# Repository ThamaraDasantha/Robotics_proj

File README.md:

# Robotics_proj

Roboarm algoritham - 
    Esp32 wifi conncet to mobile
Mortor Controller algoritham - 
    
Edeg ditection algoritham -

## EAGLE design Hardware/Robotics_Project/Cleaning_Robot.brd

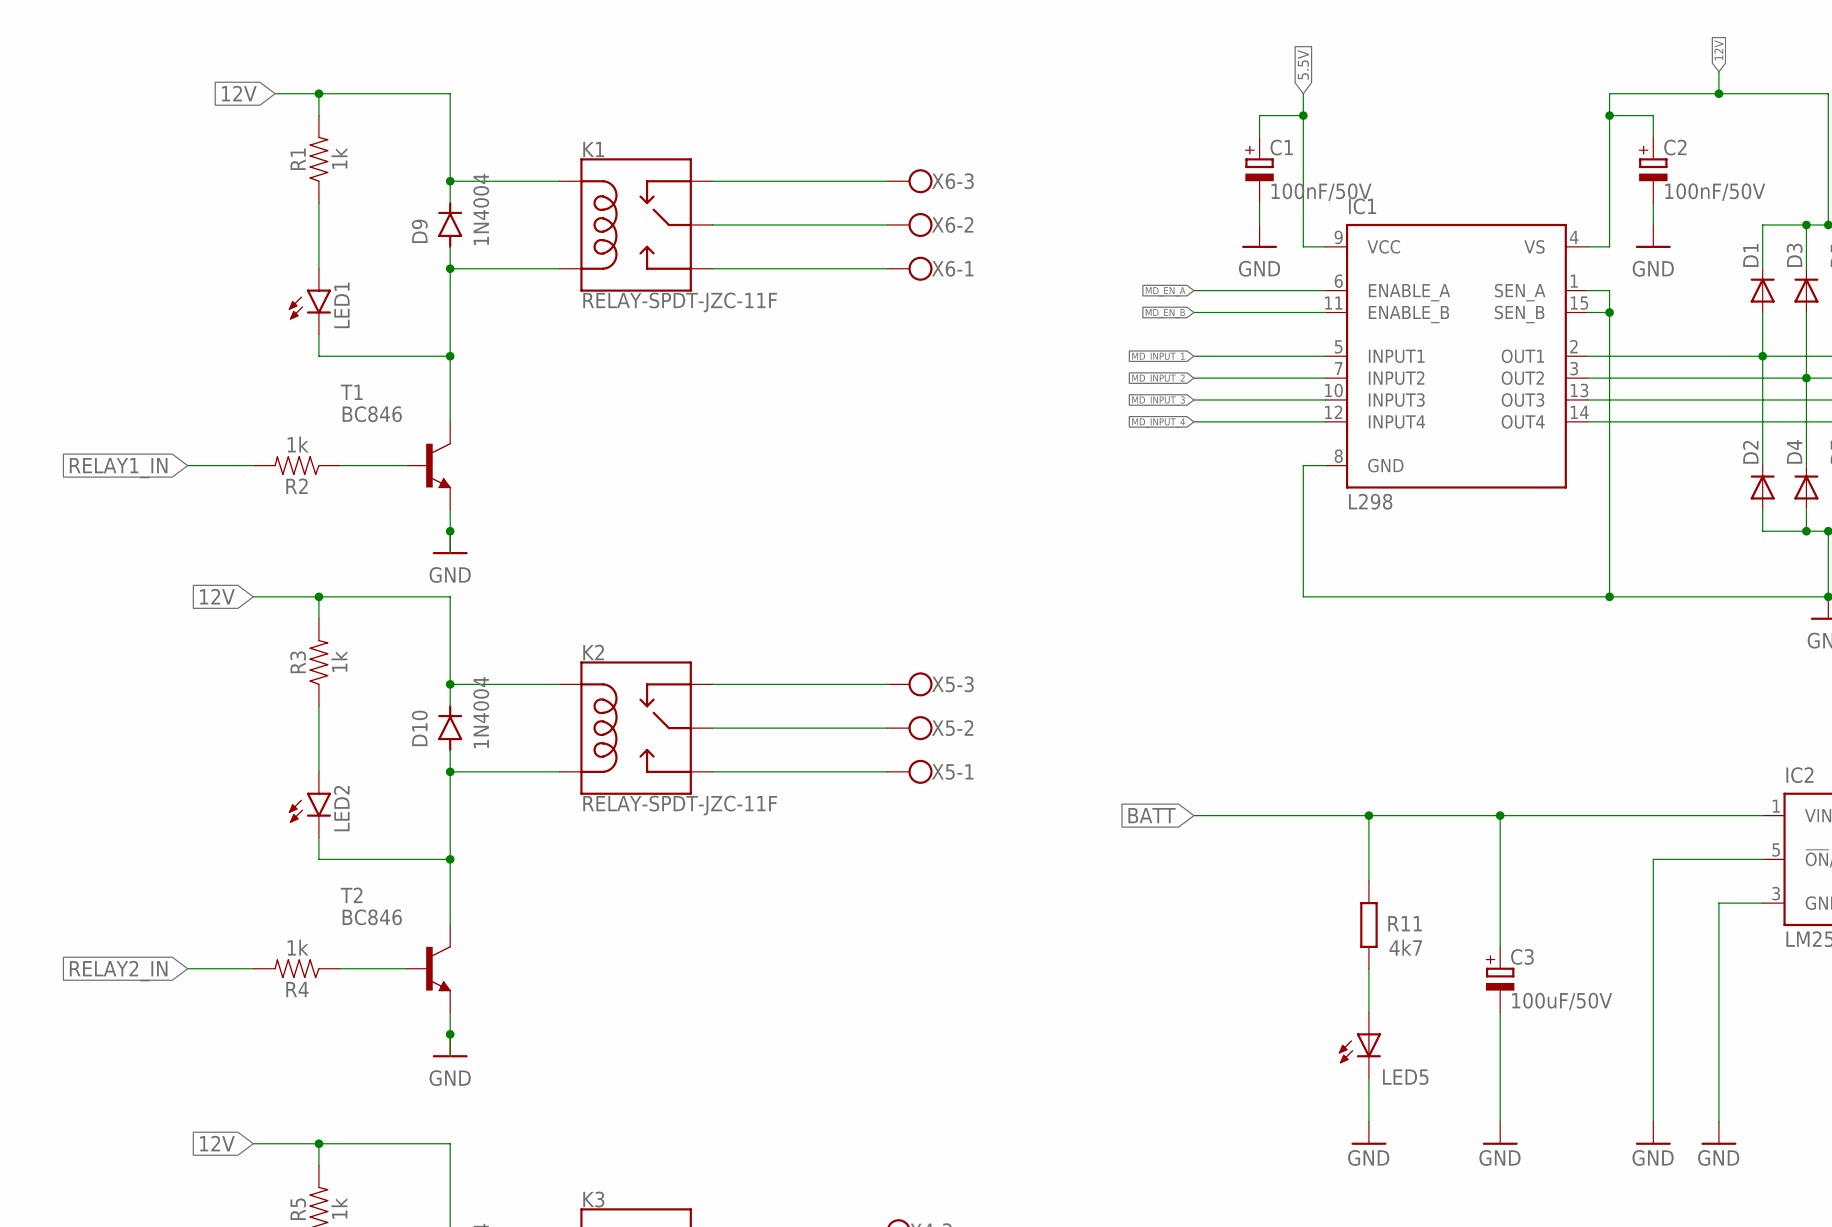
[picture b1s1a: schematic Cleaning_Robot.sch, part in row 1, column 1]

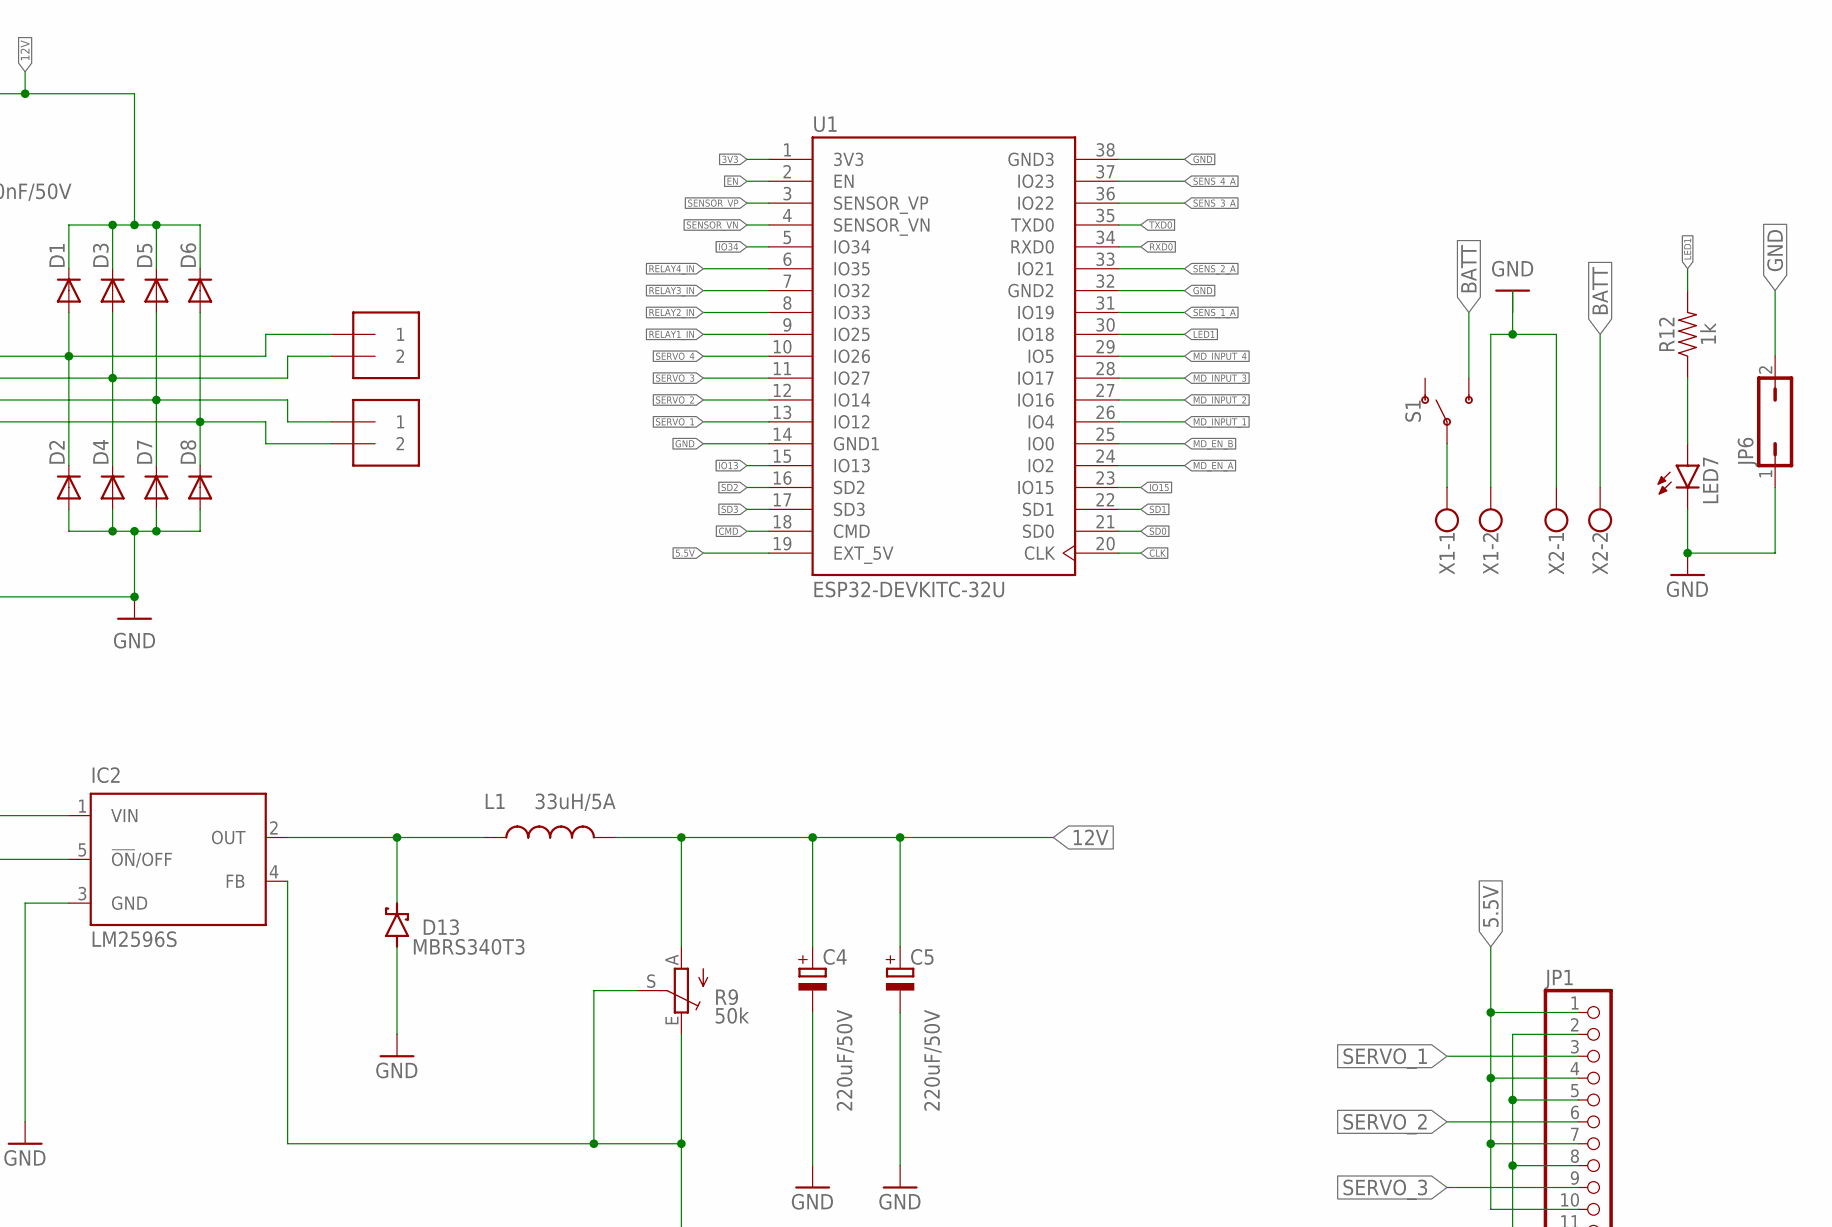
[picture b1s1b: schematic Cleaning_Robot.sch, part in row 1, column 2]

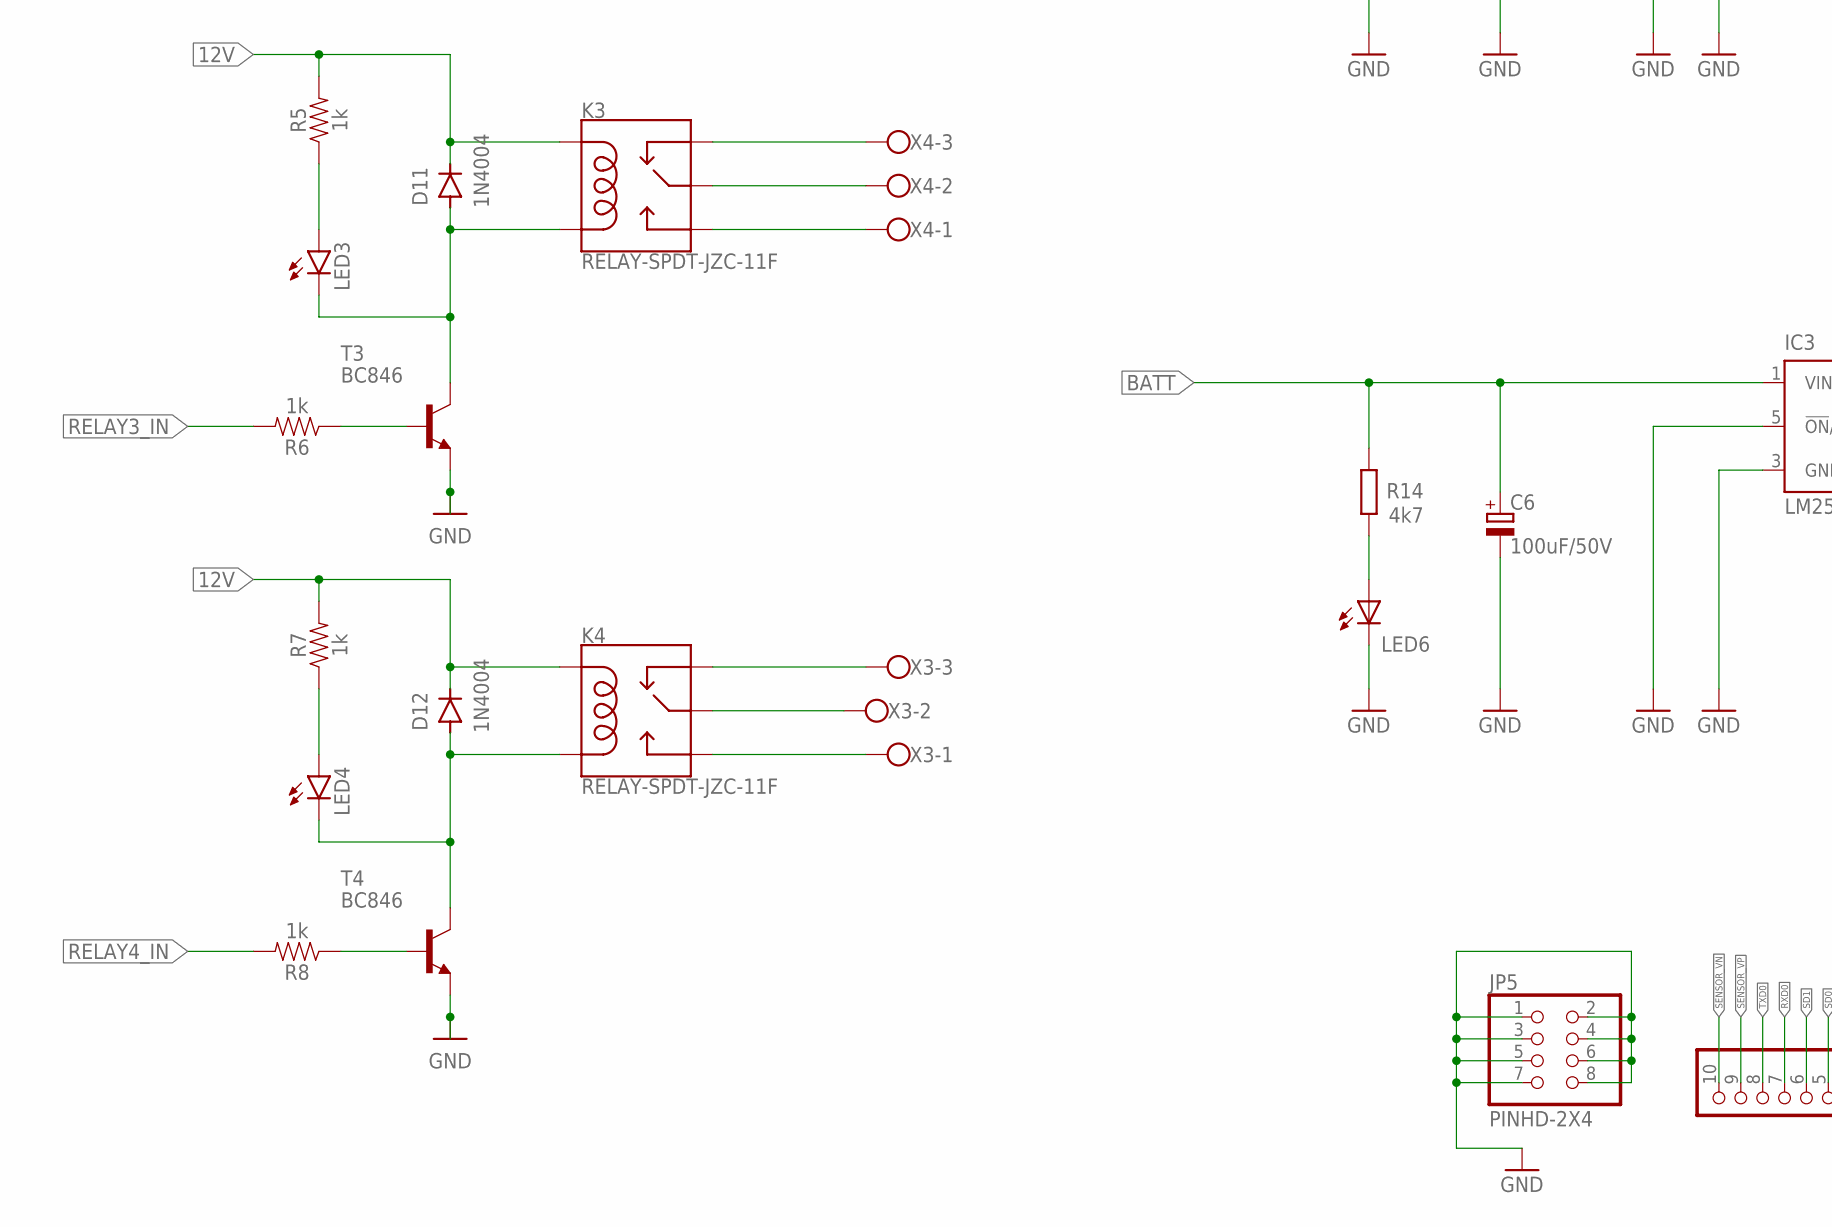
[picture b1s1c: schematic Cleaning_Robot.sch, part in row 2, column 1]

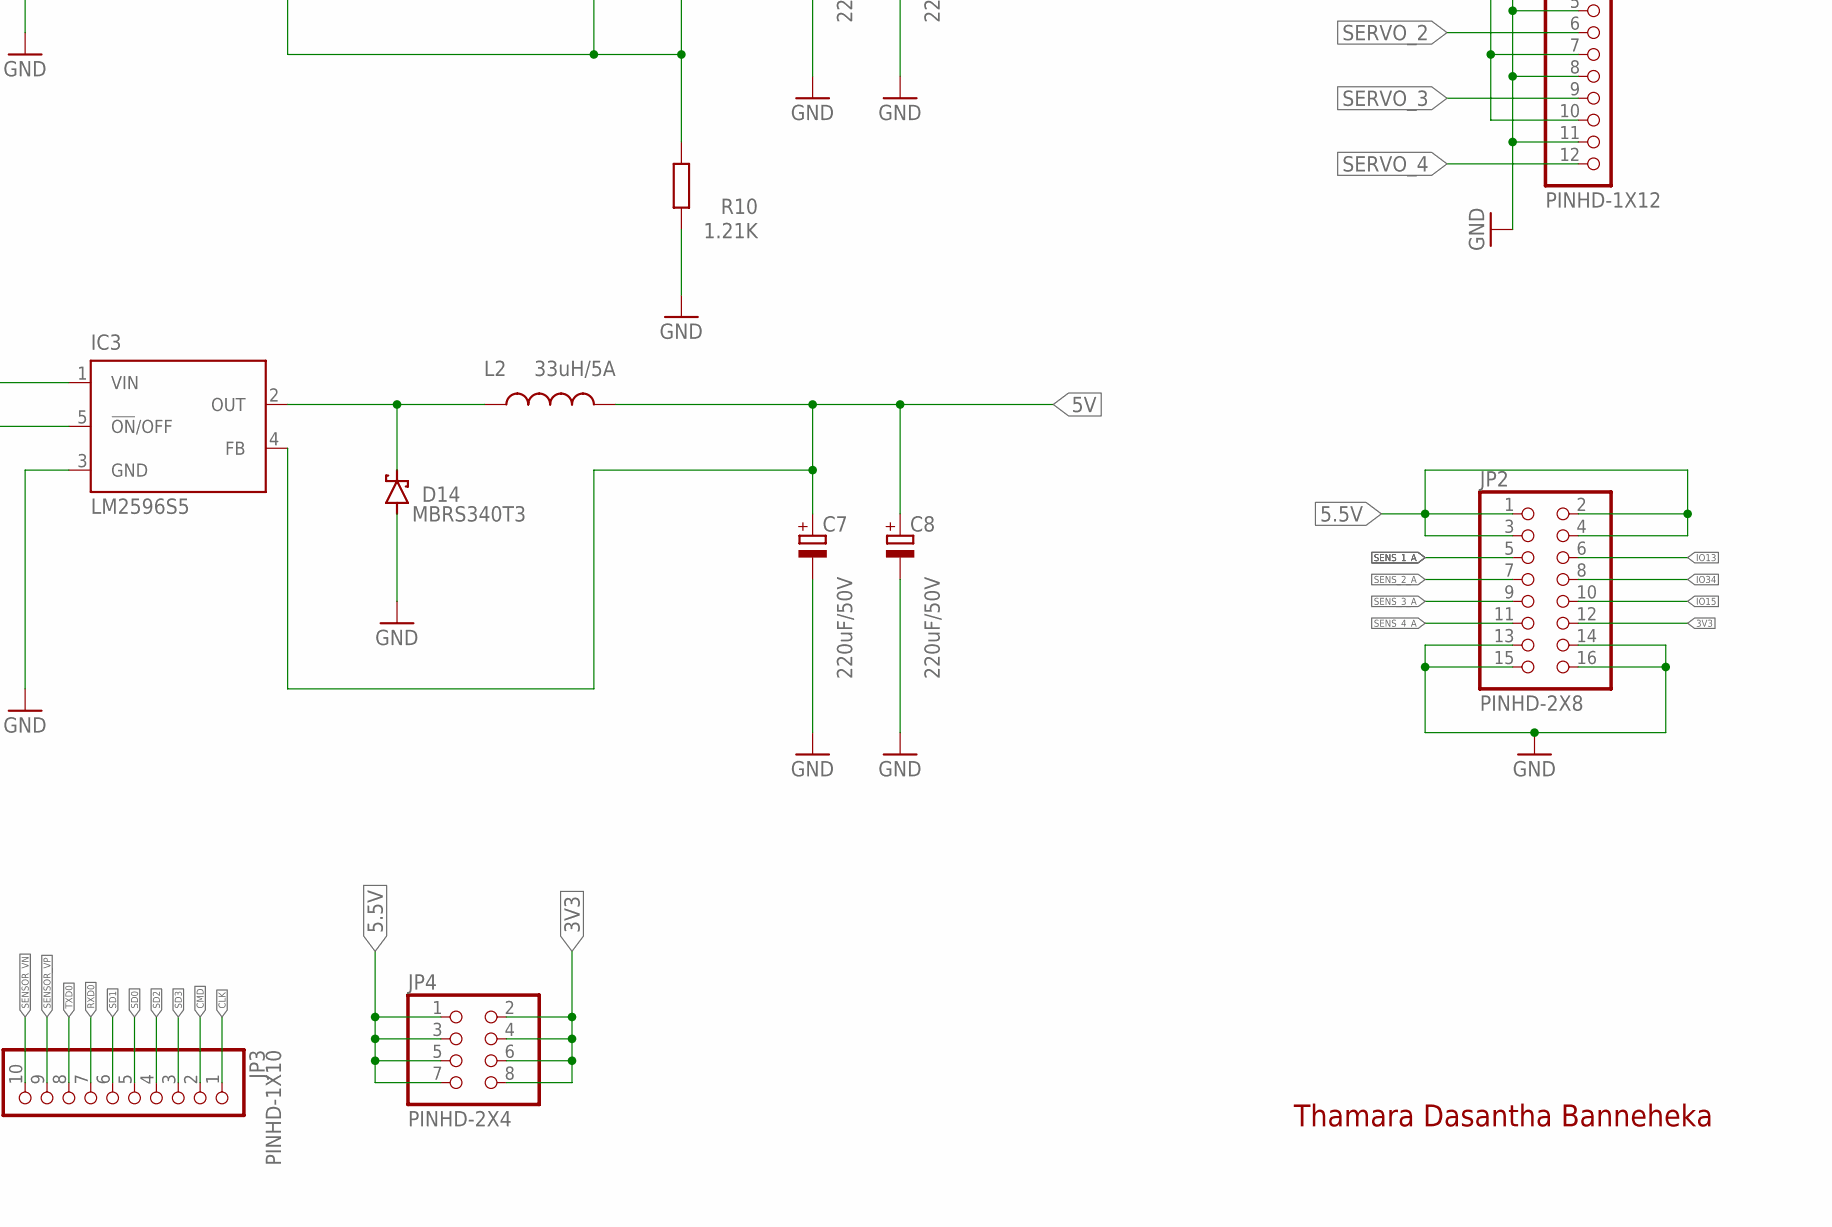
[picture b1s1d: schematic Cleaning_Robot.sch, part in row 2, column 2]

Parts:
C1, C2: 100nF/50V; 153CLV-0405
C3, C6: 100uF/50V; 153CLV-0810
C4, C5: 220uF/50V; 140CLH-1010
C7, C8: 220uF/50V; 153CLV-1010
D1, D2, D3, D4, D5, D6, D7, D8: DIODE-SOD123; SOD123
D9, D10, D11, D12: 1N4004; DO-41
D13, D14: MBRS340T3; SMC
IC1: L298; MULTIWATT-15
IC2: LM2596S; TO263-5
IC3: LM2596S5; TO263-5
J2, J3: 1X2-3.5MM
JP1: PINHD-1X12; 1X12
JP2: PINHD-2X8; 2X08
JP3: PINHD-1X10; 1X10
JP4, JP5: PINHD-2X4; 2X04
JP6: JP1Q; JP1
K1, K2, K3, K4: RELAY-SPDT-JZC-11F; RELAY-JZC
L1, L2: 33uH/5A; CDRH125
LED1, LED2, LED3, LED4, LED7: LEDCHIP-LED0805; CHIP-LED0805
LED5, LED6: LEDCHIPLED_0805; CHIPLED_0805
R1, R2, R3, R4, R5, R6, R7, R8, R12: 1k; 0805
R9: 50k; S64W
R10: 1.21K; R0805
R11, R14: 4k7; R0805
S1: SWITCH-SPDT-PTH-11.6X4.0MM-KIT; SWITCH_SPDT_PTH_11.6X4.0MM_KIT
T1, T2, T3, T4: BC846; SOT23
U1: ESP32-DEVKITC-32U; MODULE_ESP32-DEVKITC-32U
X1, X2: W237-102
X3, X4, X5, X6: W237-103

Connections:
3V3: JP2.12, JP4.2, JP4.4, JP4.6, JP4.8, U1.1 (3V3)
5.5V: C1.+, IC1.9 (VCC), JP1.1, JP1.4, JP1.7, JP1.10, JP2.1, JP2.2, JP2.3, JP2.4, JP4.1, JP4.3, JP4.5, JP4.7, U1.19 (EXT_5V)
5V: C7.+, C8.+, IC3.4 (FB), L2.2
12V: C2.+, C4.+, C5.+, D1.C, D3.C, D5.C, D6.C, D9.C, D10.C, D11.C, D12.C, IC1.4 (VS), K1.5 (COIL1), K2.5 (COIL1), K3.5 (COIL1), K4.5 (COIL1), L1.2, R1.2, R3.2, R5.2, R7.2, R9.A
BATT: C3.+, C6.+, IC2.1 (VIN), IC3.1 (VIN), R11.2, R14.2, S1.3 (S), X2.2
CLK: JP3.1, U1.20 (CLK)
CMD: JP3.2, U1.18 (CMD)
COM: K1.4 (MAIN), K2.4 (MAIN), K3.4 (MAIN), X4.2, X5.2, X6.2
EN: U1.2 (EN)
GND: C1.-, C2.-, C3.-, C4.-, C5.-, C6.-, C7.-, C8.-, D2.A, D4.A, D7.A, D8.A, D13.A, D14.A, IC1.1 (SEN_A), IC1.8 (GND), IC1.15 (SEN_B), IC2.3 (GND), IC2.5 (!ON!/OFF), IC3.3 (GND), IC3.5 (!ON!/OFF), JP1.2, JP1.5, JP1.8, JP1.11, JP2.13, JP2.14, JP2.15, JP2.16, JP5.1, JP5.2, JP5.3, JP5.4, JP5.5, JP5.6, JP5.7, JP5.8, JP6.1, JP6.2, LED5.C, LED6.C, LED7.C, R10.1, T1.2 (E), T2.2 (E), T3.2 (E), T4.2 (E), U1.14 (GND1), U1.32 (GND2), U1.38 (GND3), X1.2, X2.1
IO13: JP2.6, U1.15 (IO13)
IO15: JP2.10, U1.23 (IO15)
IO34: JP2.8, U1.5 (IO34)
LED1: R12.2, U1.30 (IO18)
MD_EN_A: IC1.6 (ENABLE_A), U1.24 (IO2)
MD_EN_B: IC1.11 (ENABLE_B), U1.25 (IO0)
MD_INPUT_1: IC1.5 (INPUT1), U1.26 (IO4)
MD_INPUT_2: IC1.7 (INPUT2), U1.27 (IO16)
MD_INPUT_3: IC1.10 (INPUT3), U1.28 (IO17)
MD_INPUT_4: IC1.12 (INPUT4), U1.29 (IO5)
unnamed: D1.A, D2.C, IC1.2 (OUT1), J2.1
unnamed: D3.A, D4.C, IC1.3 (OUT2), J2.2
unnamed: D6.A, D8.C, IC1.14 (OUT4), J3.2
unnamed: D5.A, D7.C, IC1.13 (OUT3), J3.1
unnamed: D10.A, K2.1 (COIL2), LED2.C, T2.3 (C)
unnamed: LED2.A, R3.1
unnamed: R4.1, T2.1 (B)
unnamed: D9.A, K1.1 (COIL2), LED1.C, T1.3 (C)
unnamed: D11.A, K3.1 (COIL2), LED3.C, T3.3 (C)
unnamed: LED1.A, R1.1
unnamed: LED3.A, R5.1
unnamed: R2.1, T1.1 (B)
unnamed: R6.1, T3.1 (B)
unnamed: D12.A, K4.1 (COIL2), LED4.C, T4.3 (C)
unnamed: LED4.A, R7.1
unnamed: R8.1, T4.1 (B)
unnamed: K4.2 (NC), X3.3
unnamed: D13.C, IC2.2 (OUT), L1.1
unnamed: K4.4 (MAIN), X3.2
unnamed: IC2.4 (FB), R9.E, R9.S, R10.2
unnamed: LED5.A, R11.1
unnamed: K4.3 (NO), X3.1
unnamed: D14.C, IC3.2 (OUT), L2.1
unnamed: LED6.A, R14.1
unnamed: S1.2, X1.1
unnamed: LED7.A, R12.1
NC: K1.2 (NC), K2.2 (NC), K3.2 (NC), X4.3, X5.3, X6.3
NO: K1.3 (NO), K2.3 (NO), K3.3 (NO), X4.1, X5.1, X6.1
RELAY1_IN: R2.2, U1.9 (IO25)
RELAY2_IN: R4.2, U1.8 (IO33)
RELAY3_IN: R6.2, U1.7 (IO32)
RELAY4_IN: R8.2, U1.6 (IO35)
RXD0: JP3.7, U1.34 (RXD0)
SD0: JP3.5, U1.21 (SD0)
SD1: JP3.6, U1.22 (SD1)
SD2: JP3.4, U1.16 (SD2)
SD3: JP3.3, U1.17 (SD3)
SENSOR_VN: JP3.10, U1.4 (SENSOR_VN)
SENSOR_VP: JP3.9, U1.3 (SENSOR_VP)
SENS_1_A: JP2.5, U1.31 (IO19)
SENS_2_A: JP2.7, U1.33 (IO21)
SENS_3_A: JP2.9, U1.36 (IO22)
SENS_4_A: JP2.11, U1.37 (IO23)
SERVO_1: JP1.3, U1.13 (IO12)
SERVO_2: JP1.6, U1.12 (IO14)
SERVO_3: JP1.9, U1.11 (IO27)
SERVO_4: JP1.12, U1.10 (IO26)
TXD0: JP3.8, U1.35 (TXD0)

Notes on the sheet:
Thamara Dasantha Banneheka

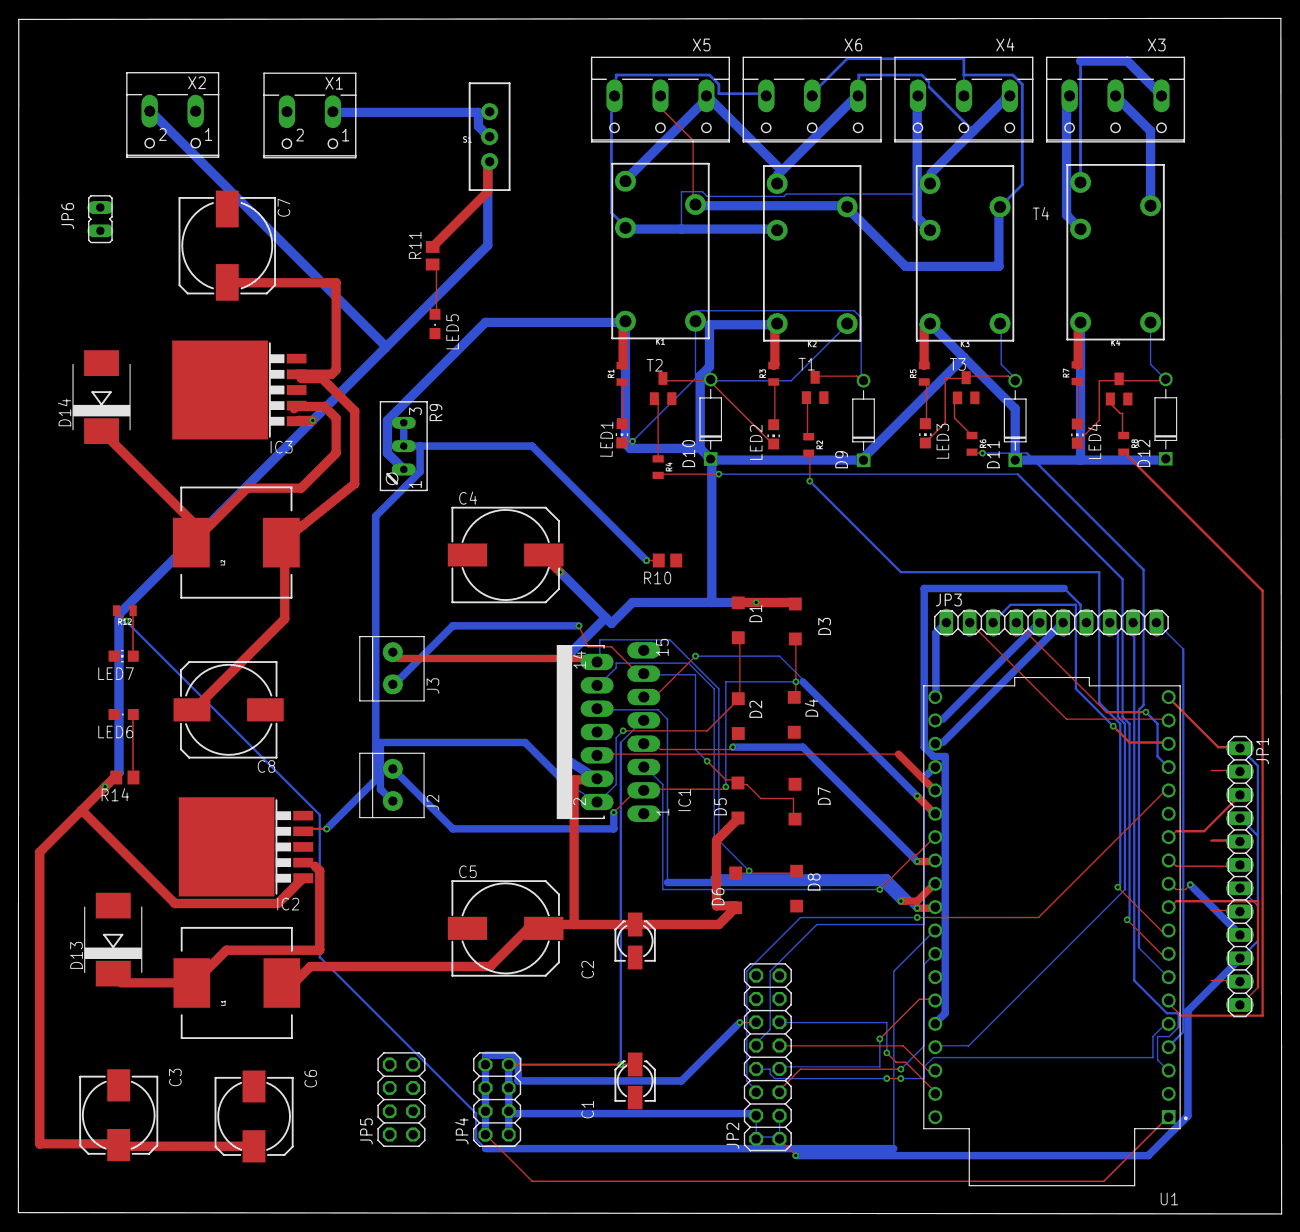
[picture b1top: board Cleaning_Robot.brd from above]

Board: 2 copper layers, 137.5 x 130.1 mm, 71 parts (0 on the bottom side), 67 nets.

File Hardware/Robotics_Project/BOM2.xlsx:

Qty | Value | Device | Package | Parts | Description
8 |  | DIODE-D-5 | D-5 | D1, D2, D3, D4, D5, D6, D7, D8 | DIODE
1 |  | JP1Q | JP1 | JP6 | JUMPER
5 |  | LEDCHIP-LED0805 | CHIP-LED0805 | LED1, LED2, LED3, LED4, LED7 | LED
2 |  | LEDCHIPLED_0805 | CHIPLED_0805 | LED5, LED6 | LED
1 | 1.21K | R-EU_R0805 | R0805 | R10 | RESISTOR, European symbol
2 | 100nF | C-US050-024X044 | C050-024X044 | C1, C2 | CAPACITOR, American symbol
2 | 100uF/50V | CPOL-EU153CLV-1010 | 153CLV-1010 | C3, C6 | POLARIZED CAPACITOR, European symbol
4 | 1N4004 | 1N4004 | DO-41 | D9, D10, D11, D12 | DIODE GEN PURP 400V 1A DO41
9 | 1k | RESISTOR0805 | 0805 | R1, R2, R3, R4, R5, R6, R7, R8, R12 | Generic Resistor Package
4 | 220uF/50V | CPOL-EU153CLV-1010 | 153CLV-1010 | C4, C5, C7, C8 | POLARIZED CAPACITOR, European symbol
2 | 33uH/5A | INDUCTORPWR | CDRH125 | L1, L2 | Inductors
2 | 4k7 | R-EU_R0805 | R0805 | R11, R14 | RESISTOR, European symbol
1 | 50k | TRIM_EU-S64W | S64W | R9 | POTENTIOMETER
4 | BC846 | BC846 | SOT23 | T1, T2, T3, T4 | NPN TRANSISTOR
1 | LM2596S | LM2596S | TO263-5 | IC2 | SIMPLE SWITCHERÂ® Power Converter 150 kHz 3A Step-Down Voltage Regulator
1 | LM2596S5 | LM2596S | TO263-5 | IC3 | SIMPLE SWITCHERÂ® Power Converter 150 kHz 3A Step-Down Voltage Regulator
2 | MBRS340T3 | MBRS340T3 | SMC | D13, D14 | SCHOTTKY BARRIER RECTIFIER 3.0 AMPERES 20, 30, 40 VOLT

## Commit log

2023-07-04 Create Code
2025-06-20 main

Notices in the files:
parts and their libraries:
SparkFun-Electromechanical: Licensing: Creative Commons ShareAlike 4.0 International - https://creativecommons.org/licenses/by-sa/4.0
SparkFun-Passives: Licensing: CC v3.0 Share-Alike You are welcome to use this library for commercial purposes.
